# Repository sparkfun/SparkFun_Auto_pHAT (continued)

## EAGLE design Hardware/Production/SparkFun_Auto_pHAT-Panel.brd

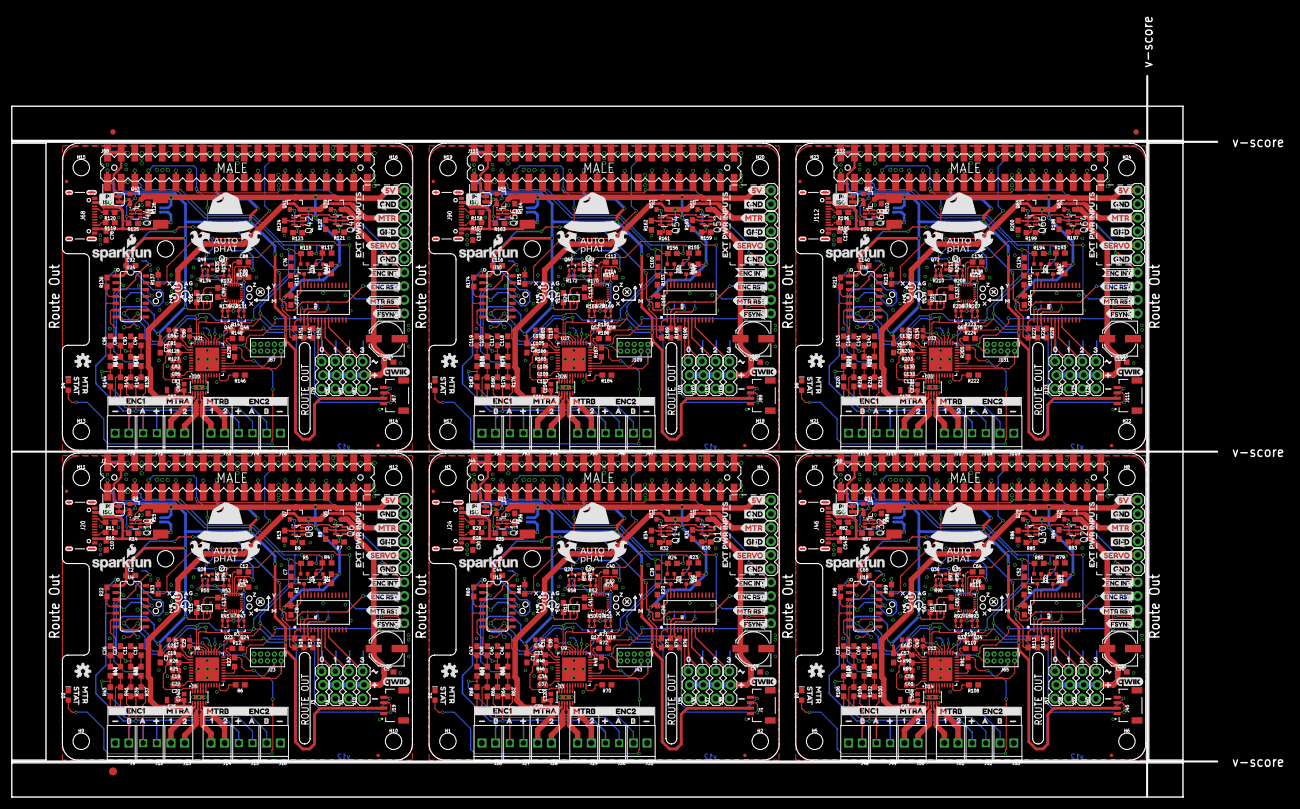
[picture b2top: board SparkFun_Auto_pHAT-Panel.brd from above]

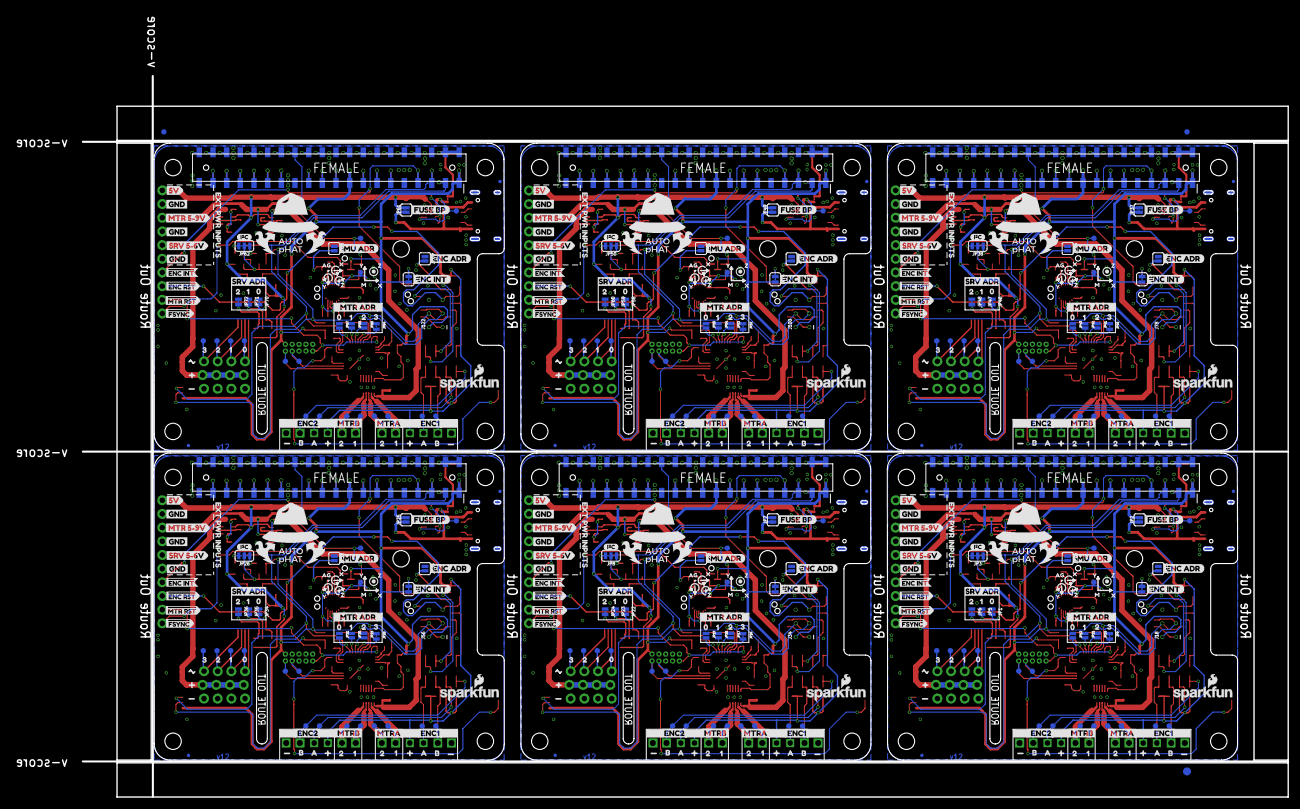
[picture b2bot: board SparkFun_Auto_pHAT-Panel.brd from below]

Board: 2 copper layers, 223.9 x 133.9 mm, 1482 parts (507 on the bottom side), 600 nets.

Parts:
C1, C2, C3, C6, C7, C8, C9, C10, C12, C13, C28, C29, C30, C40, C41, C44, C49, C51, C52, C53, C54, C64, C65, C68, C73, C75, C76, C77, C78, C88, C89, C92, C97, C99, C100, C101, C102, C112, C113, C116, C121, C123, C124, C125, C126, C136, C137, C140: 0.1uF; 0603
C4, C5, C50, C74, C98, C122: 100uF; PANASONIC_D
C11, C16, C26, C27, C45, C46, C47, C48, C69, C70, C71, C72, C93, C94, C95, C96, C117, C118, C119, C120, C141, C142, C143, C144: 10nF; 0603
C14, C15, C42, C43, C66, C67, C90, C91, C114, C115, C138, C139: 1.0uF; 0603
C17, C18, C19, C20, C31, C33, C34, C35, C55, C57, C58, C59, C79, C81, C82, C83, C103, C105, C106, C107, C127, C129, C130, C131: 1.0uF; 0402
C21, C22, C23, C24, C32, C36, C37, C38, C56, C60, C61, C62, C80, C84, C85, C86, C104, C108, C109, C110, C128, C132, C133, C134: 0.1uF; 0402
C25, C39, C63, C87, C111, C135: 10uF; 0805
D1, D2, D3, D4, D5, D6: BLUE; LED-0603@1
E$1, E$2, E$3, E$4: FIDUCIAL-1X2
E$5, E$6: FIDUCIAL-1.5X3
F1, F2, F3, F4, F5, F6: 16V/2.5A(5A TRIP); 1812
FD1, FD2, FD3, FD4, FD5, FD6, FD7, FD8, FD9, FD10, FD11, FD12, FD13, FD14, FD15, FD16, FD17, FD18, FD19, FD20, FD21, FD22, FD23, FD24: FIDUCIALUFIDUCIAL; FIDUCIAL-MICRO
FRAME1, FRAME5, FRAME8, FRAME11, FRAME14, FRAME17: FRAME-LETTERNO_PACKAGE; DUMMY
FRAME2, FRAME3, FRAME4, FRAME6, FRAME7, FRAME9, FRAME10, FRAME12, FRAME13, FRAME15, FRAME16, FRAME18: FRAME-LEDGER; CREATIVE_COMMONS
H1, H2, H3, H4, H5, H6, H7, H8, H9, H10, H11, H12, H13, H14, H15, H16, H17, H18, H19, H20, H21, H22, H23, H24: STAND-OFFTIGHT; STAND-OFF-TIGHT
INT, INT1, INT2, INT3, INT4, INT5: SMT-JUMPER_2_NC_TRACE_SILK
J1, J19, J45, J67, J89, J111: JST04_1MM_RA
J2, J44, J66, J88, J110, J132: RASPBERRYPI-40-PIN-GPIO_SMD_STACKABLE_NOHOLES; RASPBERRY_PI_HAT_40_PIN_SMD_STACKABLE_NOHOLES
J3, J4, J5, J10, J35, J36, J37, J38, J57, J58, J59, J60, J79, J80, J81, J82, J101, J102, J103, J104, J123, J124, J125, J126: 1X03_LOCK
J6, J17, J21, J22, J32, J33, J41, J42, J54, J55, J63, J64, J76, J77, J85, J86, J98, J99, J107, J108, J120, J121, J129, J130: 1X01_NO_SILK
J7, J39, J61, J83, J105, J127: EXT SERVO PWR; 1X02
J8, J40, J62, J84, J106, J128: EXT 5V PWR; 1X02
J9, J13, J14, J16, J26, J28, J29, J31, J48, J50, J51, J53, J70, J72, J73, J75, J92, J94, J95, J97, J114, J116, J117, J119: 1X02_2.54_SCREWTERM_LG_DRILL
J11, J25, J47, J69, J91, J113: EXT MTR PWR; 1X02
J12, J15, J27, J30, J49, J52, J71, J74, J93, J96, J115, J118: 1X02_2.54_SCREWTERM
J18, J34, J56, J78, J100, J122: ISP; 2X3_TEST_POINTS
J20, J24, J46, J68, J90, J112: USB C; USB-C-16P
J23, J43, J65, J87, J109, J131: CORTEX_JTAG_DEBUG_PTH; 2X5-PTH-1.27MM
JP1, JP5, JP6, JP9, JP16, JP22, JP23, JP24, JP28, JP34, JP35, JP36, JP40, JP46, JP47, JP48, JP52, JP58, JP59, JP60, JP64, JP70, JP71, JP72: JUMPER-PAD-2; SMT-JUMPER_2_NC_TRACE_NO-SILK
JP2, JP7, JP25, JP37, JP49, JP61: FUSE BP; SMT-JUMPER_2_NO_SILK
JP3, JP8, JP26, JP38, JP50, JP62: I2C; SMT-JUMPER_3_2-NC_TRACE_SILK
JP4, JP14, JP27, JP39, JP51, JP63: PI ISO; SMT-JUMPER_2_NC_TRACE_SILK
JP10, JP11, JP12, JP17, JP18, JP19, JP29, JP30, JP31, JP41, JP42, JP43, JP53, JP54, JP55, JP65, JP66, JP67: JUMPER-PAD-2; SMT-JUMPER_2_NO_NO-SILK
JP13, JP15, JP20, JP21, JP32, JP33, JP44, JP45, JP56, JP57, JP68, JP69: ADR; SMT-JUMPER_2_NO_SILK
LOGO1, LOGO3, LOGO4, LOGO6, LOGO7, LOGO9, LOGO10, LOGO12, LOGO13, LOGO15, LOGO16, LOGO18: SFE_LOGO_NAME_FLAME.1_INCH; SFE_LOGO_NAME_FLAME_.1
LOGO2, LOGO5, LOGO8, LOGO11, LOGO14, LOGO17: OSHW-LOGOS; OSHW-LOGO-S
Q1, Q2, Q3, Q4, Q21, Q22, Q37, Q38, Q49, Q50, Q61, Q62: 310mA/60V/1.6Ω; SOT323
Q5, Q7, Q9, Q11, Q13, Q15, Q25, Q29, Q31, Q39, Q41, Q43, Q51, Q53, Q55, Q63, Q65, Q67: 20V/4.2A/52mΩ/1.4W; SOT23-3
Q6, Q8, Q10, Q12, Q14, Q16, Q26, Q30, Q32, Q40, Q42, Q44, Q52, Q54, Q56, Q64, Q66, Q68: SOT363_PHILIPS
Q17, Q18, Q19, Q20, Q23, Q24, Q27, Q28, Q33, Q34, Q35, Q36, Q45, Q46, Q47, Q48, Q57, Q58, Q59, Q60, Q69, Q70, Q71, Q72: 20V/0.2A/8MHz/1.2Ω/1Vth; SOT-416FL
R1, R2, R4, R5, R8, R13, R15, R17, R18, R19, R20, R21, R22, R23, R24, R31, R33, R34, R36, R37, R38, R39, R40, R41, R42, R43, R44, R60, R61, R62, R63, R64, R65, R66, R67, R68, R69, R74, R75, R76, R77, R78, R79, R80, R84, R86, R88, R98, R99, R100, R101, R102, R103, R104, R105, R106, R107, R112, R113, R114, R115, R116, R117, R118, R122, R124, R126, R136, R137, R138, R139, R140, R141, R142, R143, R144, R145, R150, R151, R152, R153, R154, R155, R156, R160, R162, R164, R174, R175, R176, R177, R178, R179, R180, R181, R182, R183, R188, R189, R190, R191, R192, R193, R194, R198, R200, R202, R212, R213, R214, R215, R216, R217, R218, R219, R220, R221, R226, R227, R228: 10k; 0603@1
R3, R6, R10, R11, R12, R28, R29, R70, R71, R72, R81, R82, R108, R109, R110, R119, R120, R146, R147, R148, R157, R158, R184, R185, R186, R195, R196, R222, R223, R224: 5.1k; 0603@1
R7, R9, R14, R30, R32, R35, R83, R85, R87, R121, R123, R125, R159, R161, R163, R197, R199, R201: 47k; 0603@1
R16, R45, R47, R50, R51, R52, R53, R54, R55, R56, R57, R58, R59, R73, R92, R93, R94, R95, R96, R97, R111, R130, R131, R132, R133, R134, R135, R149, R168, R169, R170, R171, R172, R173, R187, R206, R207, R208, R209, R210, R211, R225: 2.2k; 0402-TIGHT
R25, R26, R46, R48, R89, R90, R127, R128, R165, R166, R203, R204: 1; 0603@1
R27, R49, R91, R129, R167, R205: 470; 0603@1
TP0, TP1, TP2, TP3, TP6, TP7, TP8, TP10, TP11, TP12, TP13, TP14, TP15, TP16, TP17, TP18, TP20, TP21, TP22, TP23, TP26, TP27, TP28, TP30, TP31, TP32, TP33, TP34, TP35, TP36, TP37, TP38, TP40, TP41, TP42, TP43, TP46, TP47, TP48, TP50, TP51, TP52, TP53, TP54, TP55, TP56, TP57, TP58, TP60, TP61, TP62, TP63, TP66, TP67, TP68, TP70, TP71, TP72, TP73, TP74, TP75, TP76, TP77, TP78, TP80, TP81, TP82, TP83, TP86, TP87, TP88, TP90, TP91, TP92, TP93, TP94, TP95, TP96, TP97, TP98, TP100, TP101, TP102, TP103, TP106, TP107, TP108, TP110, TP111, TP112, TP113, TP114, TP115, TP116, TP117, TP118: PAD.03X.04
TP4, TP5, TP19, TP24, TP25, TP39, TP44, TP45, TP59, TP64, TP65, TP79, TP84, TP85, TP99, TP104, TP105, TP119: TP_15TH
TP9, TP29, TP49, TP69, TP89, TP109: TEST-POINT3X4; PAD.03X.04
U1, U2, U13, U19, U25, U31: PCA9685; TSSOP-28_4MM
U3, U5, U14, U20, U26, U32: DRV8835; WSON-12
U4, U12, U18, U24, U30, U36: ATTINY84-ARDUINO; SO14
U6, U9, U15, U21, U27, U33: CY8C4245LQI-483; QFN-40
U7, U10, U16, U22, U28, U34: 9DoF IMU; QFN24-3X3
U8, U11, U17, U23, U29, U35: 1.8V/100mA; SC70
U$1, U$28, U$191, U$286, U$381, U$476: QWIIC_LOGO_5MM; QWIIC_5MM
U$2, U$54, U$192, U$287, U$382, U$477: I_SUPER2_C-()-03
U$3, U$4, U$5, U$59, U$60, U$61, U$114, U$115, U$116, U$160, U$161, U$162, U$218, U$219, U$220, U$255, U$256, U$257, U$313, U$314, U$315, U$350, U$351, U$352, U$408, U$409, U$410, U$445, U$446, U$447, U$503, U$504, U$505, U$540, U$541, U$542: GND3
U$6, U$7, U$75, U$76, U$142, U$143, U$172, U$173, U$237, U$238, U$267, U$268, U$332, U$333, U$362, U$363, U$427, U$428, U$457, U$458, U$522, U$523, U$552, U$553: 10
U$8, U$79, U$146, U$176, U$241, U$271, U$336, U$366, U$431, U$461, U$526, U$556: 00
U$9, U$117, U$221, U$316, U$411, U$506: #MTR_RST5
U$10, U$118, U$222, U$317, U$412, U$507: #FSYNC7
U$11, U$119, U$223, U$318, U$413, U$508: #ENC_RST4
U$12, U$120, U$224, U$319, U$414, U$509: #ENC_INT6
U$13, U$52, U$121, U$155, U$225, U$250, U$320, U$345, U$415, U$440, U$510, U$535: EXT_PWR_INPUTS3
U$14, U$131, U$226, U$321, U$416, U$511: 5V2
U$15, U$132, U$227, U$322, U$417, U$512: MTR1
U$16, U$133, U$228, U$323, U$418, U$513: SERVO0
U$17, U$82, U$147, U$179, U$242, U$274, U$337, U$369, U$432, U$464, U$527, U$559: 11
U$18, U$19, U$182, U$183, U$277, U$278, U$372, U$373, U$467, U$468, U$562, U$563: 1X06_2.54_SCREWTERM_PIN_REF
U$20, U$21, U$65, U$66, U$134, U$135, U$164, U$165, U$229, U$230, U$259, U$260, U$324, U$325, U$354, U$355, U$419, U$420, U$449, U$450, U$514, U$515, U$544, U$545: B15
U$22, U$67, U$136, U$166, U$231, U$261, U$326, U$356, U$421, U$451, U$516, U$546: ENC112
U$23, U$68, U$137, U$167, U$232, U$262, U$327, U$357, U$422, U$452, U$517, U$547: ENC213
U$24, U$80, U$148, U$177, U$243, U$272, U$338, U$367, U$433, U$462, U$528, U$557: 22
U$25, U$81, U$149, U$178, U$244, U$273, U$339, U$368, U$434, U$463, U$529, U$558: 33
U$26, U$27, U$69, U$70, U$138, U$139, U$168, U$169, U$233, U$234, U$263, U$264, U$328, U$329, U$358, U$359, U$423, U$424, U$453, U$454, U$518, U$519, U$548, U$549: A14
U$29, U$64, U$195, U$290, U$385, U$480: STAT4
U$30, U$184, U$279, U$374, U$469, U$564: SRV_5#6V1
U$31, U$73, U$140, U$170, U$235, U$265, U$330, U$360, U$425, U$455, U$520, U$550: MTRA0
U$32, U$55, U$193, U$288, U$383, U$478: ISO1
U$33, U$41, U$71, U$186, U$196, U$281, U$291, U$376, U$386, U$471, U$481, U$566: 05
U$34, U$42, U$72, U$187, U$197, U$282, U$292, U$377, U$387, U$472, U$482, U$567: 16
U$35, U$63, U$194, U$289, U$384, U$479: PI0
U$36, U$45, U$84, U$188, U$198, U$283, U$293, U$378, U$388, U$473, U$483, U$568: 27
U$37, U$86, U$199, U$294, U$389, U$484: 38
U$38, U$185, U$280, U$375, U$470, U$565: MTR_5#9V0
U$39, U$153, U$248, U$343, U$438, U$533: IMU_ADR9
U$40, U$74, U$141, U$171, U$236, U$266, U$331, U$361, U$426, U$456, U$521, U$551: MTRB1
U$43, U$44, U$77, U$78, U$144, U$145, U$174, U$175, U$239, U$240, U$269, U$270, U$334, U$335, U$364, U$365, U$429, U$430, U$459, U$460, U$524, U$525, U$554, U$555: 21
U$46, U$189, U$284, U$379, U$474, U$569: MTR0
U$47, U$190, U$285, U$380, U$475, U$570: SRV_ADR0
U$48, U$150, U$245, U$340, U$435, U$530: ENC_INT12
U$49, U$151, U$246, U$341, U$436, U$531: ENC_ADR11
U$50, U$152, U$247, U$342, U$437, U$532: FUSE_BP10
U$51, U$154, U$249, U$344, U$439, U$534: MTR_ADR0
U$53, U$156, U$251, U$346, U$441, U$536: 5V3
U$56, U$157, U$252, U$347, U$442, U$537: #ENC_RST6
U$57, U$158, U$253, U$348, U$443, U$538: #MTR_RST7
U$58, U$159, U$254, U$349, U$444, U$539: #FSYNC8
U$62, U$163, U$258, U$353, U$448, U$543: #ENC_INT0
U$83, U$85, U$180, U$181, U$275, U$276, U$370, U$371, U$465, U$466, U$560, U$561: AUTOHAT-LOGO
U$87, U$93, U$97, U$100, U$103, U$109, U$123, U$126, U$200, U$206, U$210, U$213, U$295, U$301, U$305, U$308, U$390, U$396, U$400, U$403, U$485, U$491, U$495, U$498: X0
U$88, U$94, U$98, U$101, U$104, U$110, U$124, U$127, U$201, U$207, U$211, U$214, U$296, U$302, U$306, U$309, U$391, U$397, U$401, U$404, U$486, U$492, U$496, U$499: Y1
U$89, U$95, U$99, U$102, U$105, U$111, U$125, U$128, U$202, U$208, U$212, U$215, U$297, U$303, U$307, U$310, U$392, U$398, U$402, U$405, U$487, U$493, U$497, U$500: Z2
U$90, U$106, U$112, U$129, U$203, U$216, U$298, U$311, U$393, U$406, U$488, U$501: G5
U$91, U$107, U$113, U$130, U$204, U$217, U$299, U$312, U$394, U$407, U$489, U$502: A4
U$92, U$96, U$108, U$122, U$205, U$209, U$300, U$304, U$395, U$399, U$490, U$494: M3

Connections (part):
1.8V: C13.1, C14.1, Q23.1, Q24.1, Q27.1, Q28.1, R16.2, R45.2, R47.2, R53.2, R55.2, TP9.P$1, U7.8, U7.13, U7.22, U8.5
1.8V1: C41.1, C42.1, Q17.1, Q18.1, Q19.1, Q20.1, R50.2, R51.2, R52.2, R58.2, R73.2, TP29.P$1, U10.8, U10.13, U10.22, U11.5
1.8V2: C65.1, C66.1, Q33.1, Q34.1, Q35.1, Q36.1, R92.2, R93.2, R94.2, R96.2, R111.2, TP49.P$1, U16.8, U16.13, U16.22, U17.5
1.8V3: C89.1, C90.1, Q45.1, Q46.1, Q47.1, Q48.1, R130.2, R131.2, R132.2, R134.2, R149.2, TP69.P$1, U22.8, U22.13, U22.22, U23.5
1.8V4: C113.1, C114.1, Q57.1, Q58.1, Q59.1, Q60.1, R168.2, R169.2, R170.2, R172.2, R187.2, TP89.P$1, U28.8, U28.13, U28.22, U29.5
1.8V5: C137.1, C138.1, Q69.1, Q70.1, Q71.1, Q72.1, R206.2, R207.2, R208.2, R210.2, R225.2, TP109.P$1, U34.8, U34.13, U34.22, U35.5
3.3V: C2.1, C3.1, C7.1, C15.1, INT.2, J2.1, J2.1B, J2.17, J2.17B, J12.P2, J15.P1, J18.2, J19.2, J23.1, JP3.2, Q1.1, Q4.1, R3.2, R12.2, R22.2, R25.2, R26.2, R37.2, R39.2, R41.2, R43.1, R54.2, R56.2, TP19.P$1, U4.1, U5.12, U8.1, U8.3
3.3V1: C1.1, C28.1, C43.1, C44.1, INT1.2, J1.2, J27.P2, J30.P1, J34.2, J43.1, J44.1, J44.1B, J44.17, J44.17B, JP8.2, Q2.1, Q3.1, R46.2, R48.2, R57.2, R59.2, R60.2, R62.2, R64.2, R66.2, R68.1, R71.2, R72.2, TP39.P$1, U3.12, U11.1, U11.3, U12.1
3.3V2: C49.1, C52.1, C67.1, C68.1, INT2.2, J45.2, J49.P2, J52.P1, J56.2, J65.1, J66.1, J66.1B, J66.17, J66.17B, JP26.2, Q21.1, Q22.1, R89.2, R90.2, R95.2, R97.2, R98.2, R100.2, R102.2, R104.2, R106.1, R109.2, R110.2, TP59.P$1, U14.12, U17.1, U17.3, U18.1
3.3V3: C73.1, C76.1, C91.1, C92.1, INT3.2, J67.2, J71.P2, J74.P1, J78.2, J87.1, J88.1, J88.1B, J88.17, J88.17B, JP38.2, Q37.1, Q38.1, R127.2, R128.2, R133.2, R135.2, R136.2, R138.2, R140.2, R142.2, R144.1, R147.2, R148.2, TP79.P$1, U20.12, U23.1, U23.3, U24.1
3.3V4: C97.1, C100.1, C115.1, C116.1, INT4.2, J89.2, J93.P2, J96.P1, J100.2, J109.1, J110.1, J110.1B, J110.17, J110.17B, JP50.2, Q49.1, Q50.1, R165.2, R166.2, R171.2, R173.2, R174.2, R176.2, R178.2, R180.2, R182.1, R185.2, R186.2, TP99.P$1, U26.12, U29.1, U29.3, U30.1
3.3V5: C121.1, C124.1, C139.1, C140.1, INT5.2, J111.2, J115.P2, J118.P1, J122.2, J131.1, J132.1, J132.1B, J132.17, J132.17B, JP62.2, Q61.1, Q62.1, R203.2, R204.2, R209.2, R211.2, R212.2, R214.2, R216.2, R218.2, R220.1, R223.2, R224.2, TP119.P$1, U32.12, U35.1, U35.3, U36.1
5V: C8.1, F2.2, J8.2, JP2.2, Q5.3, Q6.1, Q7.3, Q8.1, Q9.3, Q10.1, R1.2, R2.2, R17.2, R18.2, R19.2, U1.28
5V1: C29.1, F1.2, J40.2, JP7.2, Q11.3, Q12.1, Q13.3, Q14.1, Q15.3, Q16.1, R20.2, R21.2, R74.2, R75.2, R76.2, U2.28
5V2: C53.1, F3.2, J62.2, JP25.2, Q25.3, Q26.1, Q29.3, Q30.1, Q31.3, Q32.1, R77.2, R78.2, R112.2, R113.2, R114.2, U13.28
5V3: C77.1, F4.2, J84.2, JP37.2, Q39.3, Q40.1, Q41.3, Q42.1, Q43.3, Q44.1, R115.2, R116.2, R150.2, R151.2, R152.2, U19.28
5V4: C101.1, F5.2, J106.2, JP49.2, Q51.3, Q52.1, Q53.3, Q54.1, Q55.3, Q56.1, R153.2, R154.2, R188.2, R189.2, R190.2, U25.28
5V5: C125.1, F6.2, J128.2, JP61.2, Q63.3, Q64.1, Q65.3, Q66.1, Q67.3, Q68.1, R191.2, R192.2, R226.2, R227.2, R228.2, U31.28
!ENC_INT: J2.7, J2.7B, J6.1, R33.1, U4.13
!ENC_INT1: J32.1, J44.7, J44.7B, R61.1, U12.13
!ENC_INT2: J54.1, J66.7, J66.7B, R99.1, U18.13
!ENC_INT3: J76.1, J88.7, J88.7B, R137.1, U24.13
!ENC_INT4: J98.1, J110.7, J110.7B, R175.1, U30.13
!ENC_INT5: J120.1, J132.7, J132.7B, R213.1, U36.13
!ENC_RST: J17.1, J18.5, R22.1, U4.4
!ENC_RST1: J33.1, J34.5, R60.1, U12.4
!ENC_RST2: J55.1, J56.5, R98.1, U18.4
!ENC_RST3: J77.1, J78.5, R136.1, U24.4
!ENC_RST4: J99.1, J100.5, R174.1, U30.4
!ENC_RST5: J121.1, J122.5, R212.1, U36.4
!FSYNC_1.8V: Q27.2, R53.1, U7.11
!FSYNC_1.8V1: Q19.2, R52.1, U10.11
!FSYNC_1.8V2: Q35.2, R94.1, U16.11
!FSYNC_1.8V3: Q47.2, R132.1, U22.11
!FSYNC_1.8V4: Q59.2, R170.1, U28.11
!FSYNC_1.8V5: Q71.2, R208.1, U34.11
!FSYNC_3.3V: J21.1, Q27.3, R54.1
!FSYNC_3.3V1: J41.1, Q19.3, R57.1
!FSYNC_3.3V2: J63.1, Q35.3, R95.1
!FSYNC_3.3V3: J85.1, Q47.3, R133.1
!FSYNC_3.3V4: J107.1, Q59.3, R171.1
!FSYNC_3.3V5: J129.1, Q71.3, R209.1
!MTR_RST: C23.1, J22.1, J23.10, U6.30
!MTR_RST1: C38.1, J42.1, J43.10, U9.30
!MTR_RST2: C62.1, J64.1, J65.10, U15.30
!MTR_RST3: C86.1, J86.1, J87.10, U21.30
!MTR_RST4: C110.1, J108.1, J109.10, U27.30
!MTR_RST5: C134.1, J130.1, J131.10, U33.30
AD0/SDO: JP15.2, R16.1, U7.9
AD0/SDO1: JP20.2, R73.1, U10.9
AD0/SDO2: JP32.2, R111.1, U16.9
AD0/SDO3: JP44.2, R149.1, U22.9
AD0/SDO4: JP56.2, R187.1, U28.9
AD0/SDO5: JP68.2, R225.1, U34.9
ADD_A0: JP1.2, R18.1, U1.1
ADD_A1: JP5.2, R17.1, U1.2
ADD_A2: JP6.2, R19.1, U1.3
ADD_A3: JP23.2, R74.1, U2.2
ADD_A4: JP22.2, R75.1, U2.1
ADD_A5: JP24.2, R76.1, U2.3
ADD_A6: JP35.2, R112.1, U13.2
ADD_A7: JP34.2, R113.1, U13.1
ADD_A8: JP36.2, R114.1, U13.3
ADD_A9: JP47.2, R150.1, U19.2
ADD_A10: JP46.2, R151.1, U19.1
ADD_A11: JP48.2, R152.1, U19.3
ADD_A12: JP59.2, R188.1, U25.2
ADD_A13: JP58.2, R189.1, U25.1
ADD_A14: JP60.2, R190.1, U25.3
ADD_A15: JP71.2, R226.1, U31.2
ADD_A16: JP70.2, R227.1, U31.1
ADD_A17: JP72.2, R228.1, U31.3
ADR: JP13.2, U4.3
ADR1: JP21.2, U12.3
ADR2: JP33.2, U18.3
ADR3: JP45.2, U24.3
ADR4: JP57.2, U30.3
ADR5: JP69.2, U36.3
AOUT1: J13.P1, TP16.P$1, U5.2
AOUT2: J13.P2, TP15.P$1, U5.3
AOUT3: J28.P1, TP36.P$1, U3.2
AOUT4: J28.P2, TP35.P$1, U3.3
AOUT5: J50.P1, TP56.P$1, U14.2
AOUT6: J50.P2, TP55.P$1, U14.3
AOUT7: J72.P1, TP76.P$1, U20.2
AOUT8: J72.P2, TP75.P$1, U20.3
AOUT9: J94.P1, TP96.P$1, U26.2
AOUT10: J94.P2, TP95.P$1, U26.3
AOUT11: J116.P1, TP116.P$1, U32.2
AOUT12: J116.P2, TP115.P$1, U32.3
BOUT1: J14.P1, TP14.P$1, U5.4
BOUT2: J14.P2, TP13.P$1, U5.5
BOUT3: J29.P1, TP34.P$1, U3.4
BOUT4: J29.P2, TP33.P$1, U3.5
BOUT5: J51.P1, TP54.P$1, U14.4
BOUT6: J51.P2, TP53.P$1, U14.5
BOUT7: J73.P1, TP74.P$1, U20.4
BOUT8: J73.P2, TP73.P$1, U20.5
BOUT9: J95.P1, TP94.P$1, U26.4
BOUT10: J95.P2, TP93.P$1, U26.5
BOUT11: J117.P1, TP114.P$1, U32.4
BOUT12: J117.P2, TP113.P$1, U32.5
CC1: J20.A5, R11.2
CC2: J20.B5, R10.2
CC3: J24.B5, R28.2
CC4: J24.A5, R29.2
CC5: J46.B5, R81.2
CC6: J46.A5, R82.2
CC7: J68.B5, R119.2
CC8: J68.A5, R120.2
CC9: J90.B5, R157.2
CC10: J90.A5, R158.2
CC11: J112.B5, R195.2
CC12: J112.A5, R196.2
CE0: J2.24, J2.24B
CE1: J44.24, J44.24B
CE2: J66.24, J66.24B
CE3: J88.24, J88.24B
CE4: J110.24, J110.24B
CE5: J132.24, J132.24B
CH0: J3.3, TP0.P$1, U1.6
CH1: J4.3, TP1.P$1, U1.7
CH2: J5.3, TP2.P$1, U1.8
CH3: J10.3, TP3.P$1, U1.9
CH4: J38.3, TP23.P$1, U2.9
CH5: J37.3, TP22.P$1, U2.8
CH6: J36.3, TP21.P$1, U2.7
CH7: J35.3, TP20.P$1, U2.6
CH8: J60.3, TP43.P$1, U13.9
CH9: J59.3, TP42.P$1, U13.8
CH10: J58.3, TP41.P$1, U13.7
CH11: J57.3, TP40.P$1, U13.6
CH12: J82.3, TP63.P$1, U19.9
CH13: J81.3, TP62.P$1, U19.8
CH14: J80.3, TP61.P$1, U19.7
CH15: J79.3, TP60.P$1, U19.6
CH16: J104.3, TP83.P$1, U25.9
CH17: J103.3, TP82.P$1, U25.8
CH18: J102.3, TP81.P$1, U25.7
CH19: J101.3, TP80.P$1, U25.6
CH20: J126.3, TP103.P$1, U31.9
CH21: J125.3, TP102.P$1, U31.8
CH22: J124.3, TP101.P$1, U31.7
CH23: J123.3, TP100.P$1, U31.6
CONFIG_OUT: R6.2, U6.10
CONFIG_OUT1: R70.2, U9.10
CONFIG_OUT2: R108.2, U15.10
CONFIG_OUT3: R146.2, U21.10
CONFIG_OUT4: R184.2, U27.10
CONFIG_OUT5: R222.2, U33.10
ENC1A_FILTERED: C16.1, R38.2, U4.2
ENC1A_FILTERED1: C46.1, R63.2, U12.2
ENC1A_FILTERED2: C70.1, R101.2, U18.2
ENC1A_FILTERED3: C94.1, R139.2, U24.2
ENC1A_FILTERED4: C118.1, R177.2, U30.2
ENC1A_FILTERED5: C142.1, R215.2, U36.2
ENC1A_RAW: J12.P1, R37.1, R38.1, TP17.P$1
ENC1A_RAW1: J27.P1, R62.1, R63.1, TP37.P$1
ENC1A_RAW2: J49.P1, R100.1, R101.1, TP57.P$1
ENC1A_RAW3: J71.P1, R138.1, R139.1, TP77.P$1
ENC1A_RAW4: J93.P1, R176.1, R177.1, TP97.P$1
ENC1A_RAW5: J115.P1, R214.1, R215.1, TP117.P$1
ENC1B_FILTERED: C11.1, R40.1, U4.11
ENC1B_FILTERED1: C45.1, R65.1, U12.11
ENC1B_FILTERED2: C69.1, R103.1, U18.11
ENC1B_FILTERED3: C93.1, R141.1, U24.11
ENC1B_FILTERED4: C117.1, R179.1, U30.11
ENC1B_FILTERED5: C141.1, R217.1, U36.11
ENC1B_RAW: J9.P2, R39.1, R40.2, TP18.P$1
ENC1B_RAW1: J26.P2, R64.1, R65.2, TP38.P$1
ENC1B_RAW2: J48.P2, R102.1, R103.2, TP58.P$1
ENC1B_RAW3: J70.P2, R140.1, R141.2, TP78.P$1
ENC1B_RAW4: J92.P2, R178.1, R179.2, TP98.P$1
ENC1B_RAW5: J114.P2, R216.1, R217.2, TP118.P$1
ENC2A_FILTERED: C27.1, R42.2, U4.6
ENC2A_FILTERED1: C48.1, R67.2, U12.6
ENC2A_FILTERED2: C72.1, R105.2, U18.6
ENC2A_FILTERED3: C96.1, R143.2, U24.6
ENC2A_FILTERED4: C120.1, R181.2, U30.6
ENC2A_FILTERED5: C144.1, R219.2, U36.6
ENC2A_RAW: J15.P2, R41.1, R42.1, TP12.P$1
ENC2A_RAW1: J30.P2, R66.1, R67.1, TP32.P$1
ENC2A_RAW2: J52.P2, R104.1, R105.1, TP52.P$1
ENC2A_RAW3: J74.P2, R142.1, R143.1, TP72.P$1
ENC2A_RAW4: J96.P2, R180.1, R181.1, TP92.P$1
ENC2A_RAW5: J118.P2, R218.1, R219.1, TP112.P$1
ENC2B_FILTERED: C26.1, R44.1, U4.5
ENC2B_FILTERED1: C47.1, R69.1, U12.5
ENC2B_FILTERED2: C71.1, R107.1, U18.5
ENC2B_FILTERED3: C95.1, R145.1, U24.5
ENC2B_FILTERED4: C119.1, R183.1, U30.5
ENC2B_FILTERED5: C143.1, R221.1, U36.5
ENC2B_RAW: J16.P1, R43.2, R44.2, TP11.P$1
ENC2B_RAW1: J31.P1, R68.2, R69.2, TP31.P$1
ENC2B_RAW2: J53.P1, R106.2, R107.2, TP51.P$1
ENC2B_RAW3: J75.P1, R144.2, R145.2, TP71.P$1
ENC2B_RAW4: J97.P1, R182.2, R183.2, TP91.P$1
ENC2B_RAW5: J119.P1, R220.2, R221.2, TP111.P$1
GND: C2.2, C3.2, C5.-, C6.2, C7.2, C8.2, C10.2, C11.2, C12.2, C13.2, C14.2, C15.2, C16.2, C17.2, C18.2, C19.2, C20.2, C21.2, C22.2, C23.2, C24.2, C25.2, C26.2, C27.2, D2.C, J2.6, J2.6B, J2.9, J2.9B, J2.14, J2.14B, J2.20, J2.20B, J2.25, J2.25B, J2.30, J2.30B, J2.34, J2.34B, J2.39, J2.39B, J3.1, J4.1, J5.1, J7.1, J8.1, J9.P1, J10.1, J11.1, J16.P2, J18.6, J19.1, J20.GND, J20.GND2, J23.3, J23.5, J23.7, J23.9, JP1.1, JP5.1, JP6.1, JP9.1, JP10.1, JP11.1, JP12.1, JP13.1, JP15.1, R6.1, R7.1, R8.1, R9.1, R10.1, R11.1, R13.1, R14.1, R15.1, U1.4, U1.5, U1.14, U1.23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
GND1: C1.2, C4.-, C9.2, C28.2, C29.2, C30.2, C31.2, C32.2, C33.2, C34.2, C35.2, C36.2, C37.2, C38.2, C39.2, C40.2, C41.2, C42.2, C43.2, C44.2, C45.2, C46.2, C47.2, C48.2, D1.C, J1.1, J24.GND, J24.GND2, J25.1, J26.P1, J31.P2, J34.6, J35.1, J36.1, J37.1, J38.1, J39.1, J40.1, J43.3, J43.5, J43.7, J43.9, J44.6, J44.6B, J44.9, J44.9B, J44.14, J44.14B, J44.20, J44.20B, J44.25, J44.25B, J44.30, J44.30B, J44.34, J44.34B, J44.39, J44.39B, JP16.1, JP17.1, JP18.1, JP19.1, JP20.1, JP21.1, JP22.1, JP23.1, JP24.1, R28.1, R29.1, R30.1, R31.1, R32.1, R34.1, R35.1, R36.1, R70.1, U2.4, U2.5, U2.14, U2.23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
GND2: C49.2, C50.-, C51.2, C52.2, C53.2, C54.2, C55.2, C56.2, C57.2, C58.2, C59.2, C60.2, C61.2, C62.2, C63.2, C64.2, C65.2, C66.2, C67.2, C68.2, C69.2, C70.2, C71.2, C72.2, D3.C, J45.1, J46.GND, J46.GND2, J47.1, J48.P1, J53.P2, J56.6, J57.1, J58.1, J59.1, J60.1, J61.1, J62.1, J65.3, J65.5, J65.7, J65.9, J66.6, J66.6B, J66.9, J66.9B, J66.14, J66.14B, J66.20, J66.20B, J66.25, J66.25B, J66.30, J66.30B, J66.34, J66.34B, J66.39, J66.39B, JP28.1, JP29.1, JP30.1, JP31.1, JP32.1, JP33.1, JP34.1, JP35.1, JP36.1, R81.1, R82.1, R83.1, R84.1, R85.1, R86.1, R87.1, R88.1, R108.1, U13.4, U13.5, U13.14, U13.23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
GND3: C73.2, C74.-, C75.2, C76.2, C77.2, C78.2, C79.2, C80.2, C81.2, C82.2, C83.2, C84.2, C85.2, C86.2, C87.2, C88.2, C89.2, C90.2, C91.2, C92.2, C93.2, C94.2, C95.2, C96.2, D4.C, J67.1, J68.GND, J68.GND2, J69.1, J70.P1, J75.P2, J78.6, J79.1, J80.1, J81.1, J82.1, J83.1, J84.1, J87.3, J87.5, J87.7, J87.9, J88.6, J88.6B, J88.9, J88.9B, J88.14, J88.14B, J88.20, J88.20B, J88.25, J88.25B, J88.30, J88.30B, J88.34, J88.34B, J88.39, J88.39B, JP40.1, JP41.1, JP42.1, JP43.1, JP44.1, JP45.1, JP46.1, JP47.1, JP48.1, R119.1, R120.1, R121.1, R122.1, R123.1, R124.1, R125.1, R126.1, R146.1, U19.4, U19.5, U19.14, U19.23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
GND4: C97.2, C98.-, C99.2, C100.2, C101.2, C102.2, C103.2, C104.2, C105.2, C106.2, C107.2, C108.2, C109.2, C110.2, C111.2, C112.2, C113.2, C114.2, C115.2, C116.2, C117.2, C118.2, C119.2, C120.2, D5.C, J89.1, J90.GND, J90.GND2, J91.1, J92.P1, J97.P2, J100.6, J101.1, J102.1, J103.1, J104.1, J105.1, J106.1, J109.3, J109.5, J109.7, J109.9, J110.6, J110.6B, J110.9, J110.9B, J110.14, J110.14B, J110.20, J110.20B, J110.25, J110.25B, J110.30, J110.30B, J110.34, J110.34B, J110.39, J110.39B, JP52.1, JP53.1, JP54.1, JP55.1, JP56.1, JP57.1, JP58.1, JP59.1, JP60.1, R157.1, R158.1, R159.1, R160.1, R161.1, R162.1, R163.1, R164.1, R184.1, U25.4, U25.5, U25.14, U25.23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
GND5: C121.2, C122.-, C123.2, C124.2, C125.2, C126.2, C127.2, C128.2, C129.2, C130.2, C131.2, C132.2, C133.2, C134.2, C135.2, C136.2, C137.2, C138.2, C139.2, C140.2, C141.2, C142.2, C143.2, C144.2, D6.C, J111.1, J112.GND, J112.GND2, J113.1, J114.P1, J119.P2, J122.6, J123.1, J124.1, J125.1, J126.1, J127.1, J128.1, J131.3, J131.5, J131.7, J131.9, J132.6, J132.6B, J132.9, J132.9B, J132.14, J132.14B, J132.20, J132.20B, J132.25, J132.25B, J132.30, J132.30B, J132.34, J132.34B, J132.39, J132.39B, JP64.1, JP65.1, JP66.1, JP67.1, JP68.1, JP69.1, JP70.1, JP71.1, JP72.1, R195.1, R196.1, R197.1, R198.1, R199.1, R200.1, R201.1, R202.1, R222.1, U31.4, U31.5, U31.14, U31.23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
GP1: J44.29, J44.29B
GP2: J44.31, J44.31B
GP3: J44.32, J44.32B
GP4: J44.33, J44.33B
GP5: J2.29, J2.29B
GP6: J2.31, J2.31B
GP7: J44.36, J44.36B
GP8: J44.35, J44.35B
GP9: J44.38, J44.38B
GP10: J44.40, J44.40B
GP11: J44.37, J44.37B
GP12: J2.32, J2.32B
GP13: J2.33, J2.33B
GP14: J44.13, J44.13B
GP15: J44.22, J44.22B
GP16: J2.36, J2.36B
GP17: J2.11, J2.11B
GP18: J2.12, J2.12B
GP19: J2.35, J2.35B
GP20: J2.38, J2.38B
GP21: J2.40, J2.40B
GP22: J2.15, J2.15B
GP23: J2.16, J2.16B
GP24: J2.18, J2.18B
GP25: J2.22, J2.22B
GP26: J2.37, J2.37B
GP27: J2.13, J2.13B
GP28: J44.18, J44.18B
GP29: J44.16, J44.16B
GP30: J44.15, J44.15B
GP31: J44.12, J44.12B
GP32: J44.11, J44.11B
GP33: J66.29, J66.29B
GP34: J66.31, J66.31B
GP35: J66.32, J66.32B
GP36: J66.33, J66.33B
GP37: J66.36, J66.36B
GP38: J66.35, J66.35B
GP39: J66.38, J66.38B
GP40: J66.40, J66.40B
GP41: J66.37, J66.37B
GP42: J66.13, J66.13B
GP43: J66.22, J66.22B
GP44: J66.18, J66.18B
GP45: J66.16, J66.16B
GP46: J66.15, J66.15B
GP47: J66.12, J66.12B
GP48: J66.11, J66.11B
GP49: J88.29, J88.29B
GP50: J88.31, J88.31B
GP51: J88.32, J88.32B
GP52: J88.33, J88.33B
GP53: J88.36, J88.36B
GP54: J88.35, J88.35B
GP55: J88.38, J88.38B
GP56: J88.40, J88.40B
GP57: J88.37, J88.37B
GP58: J88.13, J88.13B
GP59: J88.22, J88.22B
GP60: J88.18, J88.18B
GP61: J88.16, J88.16B
GP62: J88.15, J88.15B
GP63: J88.12, J88.12B
GP64: J88.11, J88.11B
GP65: J110.29, J110.29B
GP66: J110.31, J110.31B
GP67: J110.32, J110.32B
GP68: J110.33, J110.33B
GP69: J110.36, J110.36B
GP70: J110.35, J110.35B
GP71: J110.38, J110.38B
GP72: J110.40, J110.40B
GP73: J110.37, J110.37B
GP74: J110.13, J110.13B
GP75: J110.22, J110.22B
GP76: J110.18, J110.18B
GP77: J110.16, J110.16B
GP78: J110.15, J110.15B
GP79: J110.12, J110.12B
GP80: J110.11, J110.11B
GP81: J132.29, J132.29B
GP82: J132.31, J132.31B
GP83: J132.32, J132.32B
GP84: J132.33, J132.33B
GP85: J132.36, J132.36B
GP86: J132.35, J132.35B
GP87: J132.38, J132.38B
GP88: J132.40, J132.40B
GP89: J132.37, J132.37B
GP90: J132.13, J132.13B
GP91: J132.22, J132.22B
GP92: J132.18, J132.18B
GP93: J132.16, J132.16B
GP94: J132.15, J132.15B
GP95: J132.12, J132.12B
GP96: J132.11, J132.11B
ID_SC: J2.28, J2.28B
ID_SC1: J44.28, J44.28B
ID_SC2: J66.28, J66.28B
ID_SC3: J88.28, J88.28B
ID_SC4: J110.28, J110.28B
ID_SC5: J132.28, J132.28B
ID_SD: J2.27, J2.27B
ID_SD1: J44.27, J44.27B
ID_SD2: J66.27, J66.27B
ID_SD3: J88.27, J88.27B
ID_SD4: J110.27, J110.27B
ID_SD5: J132.27, J132.27B
IMU_INT_3.3V: J2.26, J2.26B, Q28.3, R56.1, TP10.P$1
IMU_INT_3.3V1: J44.26, J44.26B, Q20.3, R59.1, TP30.P$1
IMU_INT_3.3V2: J66.26, J66.26B, Q36.3, R97.1, TP50.P$1
IMU_INT_3.3V3: J88.26, J88.26B, Q48.3, R135.1, TP70.P$1
IMU_INT_3.3V4: J110.26, J110.26B, Q60.3, R173.1, TP90.P$1
IMU_INT_3.3V5: J132.26, J132.26B, Q72.3, R211.1, TP110.P$1
INT_1.8V: Q28.2, R55.1, U7.12
INT_1.8V1: Q20.2, R58.1, U10.12
INT_1.8V2: Q36.2, R96.1, U16.12
INT_1.8V3: Q48.2, R134.1, U22.12
INT_1.8V4: Q60.2, R172.1, U28.12
INT_1.8V5: Q72.2, R210.1, U34.12
INT_R: INT.1, R33.2
INT_R1: INT1.1, R61.2
INT_R2: INT2.1, R99.2
INT_R3: INT3.1, R137.2
INT_R4: INT4.1, R175.2
INT_R5: INT5.1, R213.2
MISO: J18.1, U4.8
MISO1: J34.1, U12.8
MISO2: J56.1, U18.8
MISO3: J78.1, U24.8
MISO4: J100.1, U30.8
MISO5: J122.1, U36.8
MODEB0: JP12.2, U6.22
MODEB1: JP11.2, U6.23
MODEB2: JP10.2, U6.24
MODEB3: JP9.2, U6.25
MODEB4: JP19.2, U9.22
MODEB5: JP18.2, U9.23
MODEB6: JP17.2, U9.24
MODEB7: JP16.2, U9.25
MODEB8: JP31.2, U15.22
MODEB9: JP30.2, U15.23
MODEB10: JP29.2, U15.24
MODEB11: JP28.2, U15.25
MODEB12: JP43.2, U21.22
MODEB13: JP42.2, U21.23
MODEB14: JP41.2, U21.24
MODEB15: JP40.2, U21.25
MODEB16: JP55.2, U27.22
MODEB17: JP54.2, U27.23
MODEB18: JP53.2, U27.24
MODEB19: JP52.2, U27.25
MODEB20: JP67.2, U33.22
MODEB21: JP66.2, U33.23
MODEB22: JP65.2, U33.24
MODEB23: JP64.2, U33.25
unnamed: Q5.1, Q6.3, R7.2
unnamed: JP3.3, R4.2
unnamed: Q1.3, R2.1, U1.26
unnamed: Q4.3, R1.1, U1.27
unnamed: JP3.1, R5.2
unnamed: Q2.3, R21.1, U2.26
unnamed: Q3.3, R20.1, U2.27
unnamed: JP8.3, R23.2
unnamed: JP8.1, R24.2
unnamed: Q11.1, Q12.3, R30.2
unnamed: Q6.2, Q6.5, Q6.6, R8.2
unnamed: Q12.2, Q12.5, Q12.6, R31.2
unnamed: Q13.1, Q14.3, R32.2
unnamed: Q14.2, Q14.5, Q14.6, R34.2
unnamed: Q7.1, Q8.3, R9.2
unnamed: Q8.2, Q8.5, Q8.6, R13.2
unnamed: Q15.1, Q16.3, R35.2
unnamed: Q9.1, Q10.3, R14.2
unnamed: Q10.2, Q10.5, Q10.6, R15.2
unnamed: J2.2, J2.2B, J2.4, J2.4B, JP4.2
unnamed: Q16.2, Q16.5, Q16.6, R36.2
unnamed: J44.2, J44.2B, J44.4, J44.4B, JP14.2
unnamed: C31.1, U9.31
unnamed: C17.1, U6.31
unnamed: C19.1, C22.1, R25.1, U6.33
unnamed: C20.1, U6.40
unnamed: D2.A, R27.2
unnamed: C34.1, C37.1, R46.1, U9.33
unnamed: C12.1, U7.10
unnamed: C35.1, U9.40
unnamed: D1.A, R49.2
unnamed: C40.1, U10.10
unnamed: Q21.3, R78.1, U13.26
unnamed: Q22.3, R77.1, U13.27
unnamed: JP26.3, R79.2
unnamed: JP26.1, R80.2
unnamed: Q25.1, Q26.3, R83.2
unnamed: Q26.2, Q26.5, Q26.6, R84.2
unnamed: Q29.1, Q30.3, R85.2
unnamed: Q30.2, Q30.5, Q30.6, R86.2
unnamed: Q31.1, Q32.3, R87.2
unnamed: Q32.2, Q32.5, Q32.6, R88.2
unnamed: J66.2, J66.2B, J66.4, J66.4B, JP27.2
unnamed: C55.1, U15.31
unnamed: C58.1, C61.1, R89.1, U15.33
unnamed: C59.1, U15.40
unnamed: D3.A, R91.2
unnamed: C64.1, U16.10
unnamed: Q37.3, R116.1, U19.26
unnamed: Q38.3, R115.1, U19.27
unnamed: JP38.3, R117.2
unnamed: JP38.1, R118.2
unnamed: Q39.1, Q40.3, R121.2
unnamed: Q40.2, Q40.5, Q40.6, R122.2
unnamed: Q41.1, Q42.3, R123.2
unnamed: Q42.2, Q42.5, Q42.6, R124.2
unnamed: Q43.1, Q44.3, R125.2
unnamed: Q44.2, Q44.5, Q44.6, R126.2
unnamed: J88.2, J88.2B, J88.4, J88.4B, JP39.2
unnamed: C79.1, U21.31
unnamed: C82.1, C85.1, R127.1, U21.33
unnamed: C83.1, U21.40
unnamed: D4.A, R129.2
unnamed: C88.1, U22.10
unnamed: Q49.3, R154.1, U25.26
unnamed: Q50.3, R153.1, U25.27
unnamed: JP50.3, R155.2
unnamed: JP50.1, R156.2
unnamed: Q51.1, Q52.3, R159.2
unnamed: Q52.2, Q52.5, Q52.6, R160.2
unnamed: Q53.1, Q54.3, R161.2
unnamed: Q54.2, Q54.5, Q54.6, R162.2
unnamed: Q55.1, Q56.3, R163.2
unnamed: Q56.2, Q56.5, Q56.6, R164.2
unnamed: J110.2, J110.2B, J110.4, J110.4B, JP51.2
unnamed: C103.1, U27.31
unnamed: C106.1, C109.1, R165.1, U27.33
unnamed: C107.1, U27.40
unnamed: D5.A, R167.2
unnamed: C112.1, U28.10
unnamed: Q61.3, R192.1, U31.26
unnamed: Q62.3, R191.1, U31.27
unnamed: JP62.3, R193.2
unnamed: JP62.1, R194.2
unnamed: Q63.1, Q64.3, R197.2
unnamed: Q64.2, Q64.5, Q64.6, R198.2
unnamed: Q65.1, Q66.3, R199.2
unnamed: Q66.2, Q66.5, Q66.6, R200.2
unnamed: Q67.1, Q68.3, R201.2
unnamed: Q68.2, Q68.5, Q68.6, R202.2
unnamed: J132.2, J132.2B, J132.4, J132.4B, JP63.2
unnamed: C127.1, U33.31
unnamed: C130.1, C133.1, R203.1, U33.33
unnamed: C131.1, U33.40
unnamed: D6.A, R205.2
unnamed: C136.1, U34.10
P2.0: U5.11, U6.1
P2.1: U5.10, U6.2
P2.2: U5.9, U6.3
P2.3: U5.8, U6.4
P2.4: U5.7, U6.5
P2.5: U3.10, U9.2
P2.6: U3.9, U9.3
P2.7: U3.8, U9.4
P2.8: U3.7, U9.5
P2.9: U3.11, U9.1
P2.10: U14.10, U15.2
P2.11: U14.9, U15.3
P2.12: U14.8, U15.4
P2.13: U14.7, U15.5
P2.14: U14.11, U15.1
P2.15: U20.10, U21.2
P2.16: U20.9, U21.3
P2.17: U20.8, U21.4
P2.18: U20.7, U21.5
P2.19: U20.11, U21.1
P2.20: U26.10, U27.2
P2.21: U26.9, U27.3
P2.22: U26.8, U27.4
P2.23: U26.7, U27.5
P2.24: U26.11, U27.1
P2.25: U32.10, U33.2
P2.26: U32.9, U33.3
P2.27: U32.8, U33.4
P2.28: U32.7, U33.5
P2.29: U32.11, U33.1
P3.1: J43.2, TP27.P$1, U9.12
P3.2: J23.2, TP7.P$1, U6.12
P3.3: J23.4, TP8.P$1, U6.13
P3.4: J43.4, TP28.P$1, U9.13
P3.5: J65.2, TP47.P$1, U15.12
P3.6: J65.4, TP48.P$1, U15.13
P3.7: J87.2, TP67.P$1, U21.12
P3.8: J87.4, TP68.P$1, U21.13
P3.9: J109.2, TP87.P$1, U27.12
P3.10: J109.4, TP88.P$1, U27.13
P3.11: J131.2, TP107.P$1, U33.12
P3.12: J131.4, TP108.P$1, U33.13
PI-5V: JP4.1, Q9.2, Q10.4, TP6.P$1
PI-5V1: JP14.1, Q15.2, Q16.4, TP26.P$1
PI-5V2: JP27.1, Q31.2, Q32.4, TP46.P$1
PI-5V3: JP39.1, Q43.2, Q44.4, TP66.P$1
PI-5V4: JP51.1, Q55.2, Q56.4, TP86.P$1
PI-5V5: JP63.1, Q67.2, Q68.4, TP106.P$1
PI_MISO: J2.21, J2.21B
PI_MISO1: J44.21, J44.21B
PI_MISO2: J66.21, J66.21B
PI_MISO3: J88.21, J88.21B
PI_MISO4: J110.21, J110.21B
PI_MISO5: J132.21, J132.21B
PI_MOSI: J2.19, J2.19B
PI_MOSI1: J44.19, J44.19B
PI_MOSI2: J66.19, J66.19B
PI_MOSI3: J88.19, J88.19B
PI_MOSI4: J110.19, J110.19B
PI_MOSI5: J132.19, J132.19B
PI_RXI: J2.10, J2.10B
PI_RXI1: J44.10, J44.10B
PI_RXI2: J66.10, J66.10B
PI_RXI3: J88.10, J88.10B
PI_RXI4: J110.10, J110.10B
PI_RXI5: J132.10, J132.10B
PI_TXO: J2.8, J2.8B
PI_TXO1: J44.8, J44.8B
PI_TXO2: J66.8, J66.8B
PI_TXO3: J88.8, J88.8B
PI_TXO4: J110.8, J110.8B
PI_TXO5: J132.8, J132.8B
SCLK: J2.23, J2.23B
SCLK1: J44.23, J44.23B
SCLK2: J66.23, J66.23B
SCLK3: J88.23, J88.23B
SCLK4: J110.23, J110.23B
SCLK5: J132.23, J132.23B
SCL_1.8V: Q23.2, R45.1, U7.23
SCL_1.8V1: Q17.2, R50.1, U10.23
SCL_1.8V2: Q33.2, R92.1, U16.23
SCL_1.8V3: Q45.2, R130.1, U22.23
SCL_1.8V4: Q57.2, R168.1, U28.23
SCL_1.8V5: Q69.2, R206.1, U34.23
SCL_3.3V: J2.5, J2.5B, J18.3, J19.4, Q1.2, Q23.3, R4.1, TP4.P$1, U4.9, U6.26
SCL_3.3V1: J1.4, J34.3, J44.5, J44.5B, Q2.2, Q17.3, R23.1, TP24.P$1, U9.26, U12.9
SCL_3.3V2: J45.4, J56.3, J66.5, J66.5B, Q21.2, Q33.3, R79.1, TP44.P$1, U15.26, U18.9
SCL_3.3V3: J67.4, J78.3, J88.5, J88.5B, Q37.2, Q45.3, R117.1, TP64.P$1, U21.26, U24.9
SCL_3.3V4: J89.4, J100.3, J110.5, J110.5B, Q49.2, Q57.3, R155.1, TP84.P$1, U27.26, U30.9
SCL_3.3V5: J111.4, J122.3, J132.5, J132.5B, Q61.2, Q69.3, R193.1, TP104.P$1, U33.26, U36.9
SCL_OUT: R12.1, U6.18
SCL_OUT1: R72.1, U9.18
SCL_OUT2: R110.1, U15.18
SCL_OUT3: R148.1, U21.18
SCL_OUT4: R186.1, U27.18
SCL_OUT5: R224.1, U33.18
SDA_1.8V: Q24.2, R47.1, U7.24
SDA_1.8V1: Q18.2, R51.1, U10.24
SDA_1.8V2: Q34.2, R93.1, U16.24
SDA_1.8V3: Q46.2, R131.1, U22.24
SDA_1.8V4: Q58.2, R169.1, U28.24
SDA_1.8V5: Q70.2, R207.1, U34.24
SDA_3.3V: J2.3, J2.3B, J18.4, J19.3, Q4.2, Q24.3, R5.1, TP5.P$1, U4.7, U6.27
SDA_3.3V1: J1.3, J34.4, J44.3, J44.3B, Q3.2, Q18.3, R24.1, TP25.P$1, U9.27, U12.7
SDA_3.3V2: J45.3, J56.4, J66.3, J66.3B, Q22.2, Q34.3, R80.1, TP45.P$1, U15.27, U18.7
SDA_3.3V3: J67.3, J78.4, J88.3, J88.3B, Q38.2, Q46.3, R118.1, TP65.P$1, U21.27, U24.7
SDA_3.3V4: J89.3, J100.4, J110.3, J110.3B, Q50.2, Q58.3, R156.1, TP85.P$1, U27.27, U30.7
SDA_3.3V5: J111.3, J122.4, J132.3, J132.3B, Q62.2, Q70.3, R194.1, TP105.P$1, U33.27, U36.7
SDA_OUT: R3.1, U6.19
SDA_OUT1: R71.1, U9.19
SDA_OUT2: R109.1, U15.19
SDA_OUT3: R147.1, U21.19
SDA_OUT4: R185.1, U27.19
SDA_OUT5: R223.1, U33.19
SERVO: C5.+, C6.1, J3.2, J4.2, J5.2, J7.2, J10.2, Q5.2, Q6.4
SERVO1: C4.+, C9.1, J35.2, J36.2, J37.2, J38.2, J39.2, Q11.2, Q12.4
SERVO2: C50.+, C51.1, J57.2, J58.2, J59.2, J60.2, J61.2, Q25.2, Q26.4
SERVO3: C74.+, C75.1, J79.2, J80.2, J81.2, J82.2, J83.2, Q39.2, Q40.4
SERVO4: C98.+, C99.1, J101.2, J102.2, J103.2, J104.2, J105.2, Q51.2, Q52.4
SERVO5: C122.+, C123.1, J123.2, J124.2, J125.2, J126.2, J127.2, Q63.2, Q64.4
SLED: R27.1, U6.14
SLED1: R49.1, U9.14
SLED2: R91.1, U15.14
SLED3: R129.1, U21.14
SLED4: R167.1, U27.14
SLED5: R205.1, U33.14
VBUS: C10.1, F2.1, J20.VBUS1, J20.VBUS2, JP2.1
VBUS1: C30.1, F1.1, J24.VBUS1, J24.VBUS2, JP7.1
VBUS2: C54.1, F3.1, J46.VBUS1, J46.VBUS2, JP25.1
VBUS3: C78.1, F4.1, J68.VBUS1, J68.VBUS2, JP37.1
VBUS4: C102.1, F5.1, J90.VBUS1, J90.VBUS2, JP49.1
VBUS5: C126.1, F6.1, J112.VBUS1, J112.VBUS2, JP61.1
VDDD1: C18.1, C21.1, R26.1, U6.32
VDDD2: C33.1, C36.1, R48.1, U9.32
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
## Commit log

2020-02-05 Finalized power input options, schematic almost done, routing started
2020-02-06 Most labeling done, pwr and motor lines routed
2020-02-07 Routing done, waiting on logo from marcom
2020-02-07 version number in bottom copper
2020-02-10 vector fonts in schematic
2020-02-10 sch cleanup and drc stuff in brd
2020-02-10 removed USB C Shield polygon
    to let more GND flow under connector up to Pi Header.
2020-02-10 added product name to top silk
2020-02-10 flipped I2C label to match others, added name to bsilk, aligned other labels
2020-02-10 added fuse bits to read me
2020-02-10 Engineer 1st run of checklist
    added measures and SS path, cleaned up sch a bit more.
2020-02-10 post design review changes
    -moved TP P3.0 programming pSoc onto grid
    -Added pulldown resistor on Config line on PSoc
    -Added trestric under pSoC to avoid GND pad nubbins.
    -Added pullup resistors to SDA_OUT and SCL_OUT, as consistent with original serial controlled motor driver.
    -Switched over to design block for pi header and slots. re-routed some stuff to make it work.
2020-02-10 moved to non-altered fab limit DRC and fix GND pour to extend to top
2020-02-12 post double-check changes - ready for proto v01
    -moved TP6 to SMT pad style and on grid
    -updated tran-14386 (ideal diode) to have polarity mark outside package
    -nudged vias to avoid silk labels
2020-02-12 proto gerbers v01
2020-02-21 Connected IMU CS pin to 1.8V, Added IMU ADR PU 2.2K resistor
2020-02-21 bumped version to v10 in sch and brd
2020-02-21 moving to SMD stackable solution... 99 done
2020-02-24 Added LOGO, improved GND pour flowing
    -added LOGO to top and bottom silk
    -rerouted some traces on right side of board near the EXT headers to allow for better GND flow
    -added more gnd vias near SMD pads on stackable header package
    -removed pesky test point values in SCH
2020-02-24 Design review changes
    -added more GND stiching VIAs to middle area of board (MTR VIN trace kind of cutts top GND pour in half diagnoly)
    -rotated IMU axis labels to read same as other silk
    -separated imu axis labels on bottom silk
    -removed GND traces from Cypress thermal pad to GND pads
    -added more gnd vias under cypress
    -removed TP15 name text in SCH
2020-02-24 update single unit gerbers
2020-02-24 dimension line width to 0.008 inch
2020-02-24 added test point to 3.3V rail
2020-02-24 Cleaned up and fixed dimensions
2020-02-25 production panel and gerbers v10
2020-02-25 Renaming production file with correct name and version
2020-02-25 fixed vector font issue on servo "~"
    -bumped version to v11
    -also updated the "+" and "-" symbols on servo headers and encoder terminals (on both top silk and bottom silk) I drew everything with wires so they look clean and will hold position through the pane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
2020-02-25 removing unneeded single unit gerbers and other unneeded files
2020-02-25 renaming files to correct product name
    no other changes made, just name of files
2020-02-25 TP19 (3.3V) moved to bottom, to expose bStop
2020-02-25 panelized v11, renamed zip file for production
2020-02-25 Added missing vertical vscore on panel
2020-03-18 v12
    -moved stat LED to side for easier rework and better visibility
    -added holes to let air through to SHIM Fan (when it sits flush up to the PCB, there is no room for airflow)
    -bumped version to v12 in copper and all 3 sheets in sch
2020-03-18 Adjusted screwpin terminal fp and locations to work with 1x2s and 1x6s
2020-03-19 Design Review changes
    -Decreased 5V trace by Pi 40pin 5V header pad, to avoid tStop overlap.
    -Decreased SDA and SCL trace width to 0.007 inch near pi header (in the uppder left of board) to avoid bStop overlap on those traces.
    -Added Voltage ranges to pin labels on EXT power inputs (bottom silk labels only)
2020-03-20 Added Address jumpers for Servo IC
    -Added 3 address jumpers to Servo IC. (includes a BOM change to include 3 more 10K resistors) This will allow for up to 8 different addresses. Note, A4 and A5 are permenantly connected to GND.
    -Added address table to SCH for address jumpers.
    -increased one of the "fan" holes to allow for even more airflow using the SHIM fan.
2020-03-20 Changed SVR ADD label to SVR ADR (to match others)
2020-03-22 Checklist run #1 on v12
    -prod ids on smt 2x20
2020-03-23 v12 gerbers
2020-04-02 created sch PDF
2020-04-16 dimensions PNG and PDF
2020-04-16 contributing, issues and license
2020-04-16 updating readme
2020-04-16 Added datasheets to documents
2020-04-16 update readme with full description
2020-04-20 Added links to firmware repos, updated readme
